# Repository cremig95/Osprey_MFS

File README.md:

# Osprey_MFS
These are the files for my Osprey MFS in the newest Versions

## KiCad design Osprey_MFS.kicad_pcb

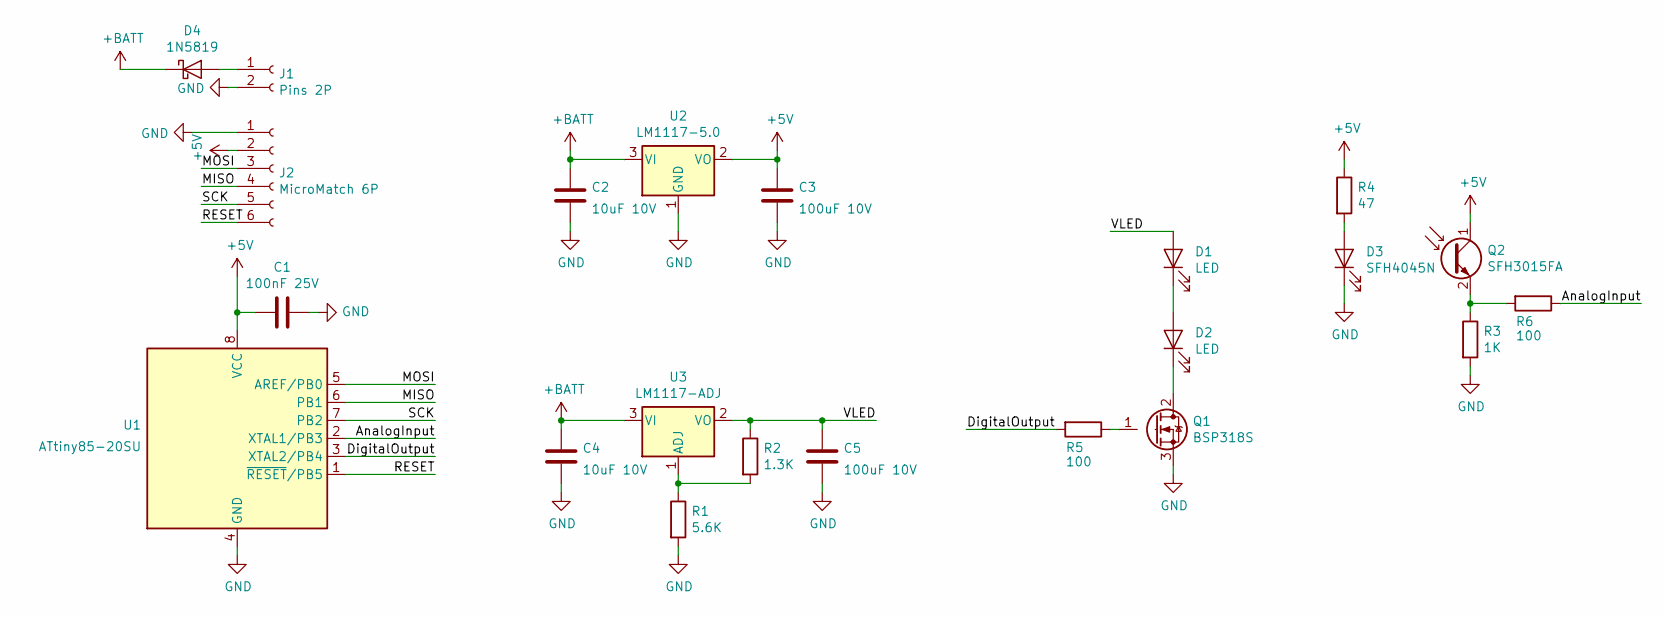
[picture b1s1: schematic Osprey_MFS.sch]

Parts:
C1: 100nF 25V; C_0603_1608Metric_Pad1.05x0.95mm_HandSolder
C2, C4: 10uF 10V; C_0603_1608Metric_Pad1.05x0.95mm_HandSolder
C3, C5: 100uF 10V; C_1210_3225Metric_Pad1.42x2.65mm_HandSolder
D1, D2: LED; LED_Cree-XQ_HandSoldering
D3: SFH4045N; LED_1210_3225Metric_Pad1.42x2.65mm_HandSolder
D4: 1N5819; D_SOD-123
J1: Pins 2P; PinHeader_1x02_P2.54mm_Vertical
J2: MicroMatch 6P; ConnectorMicromatch-6
Q1: BSP318S; SOT-223-3_TabPin2
Q2: SFH3015FA; LED_1210_3225Metric_Pad1.42x2.65mm_HandSolder
R1: 5.6K; R_0603_1608Metric_Pad1.05x0.95mm_HandSolder
R2: 1.3K; R_0603_1608Metric_Pad1.05x0.95mm_HandSolder
R3: 1K; R_0603_1608Metric_Pad1.05x0.95mm_HandSolder
R4: 47; R_0603_1608Metric_Pad1.05x0.95mm_HandSolder
R5, R6: 100; R_0603_1608Metric_Pad1.05x0.95mm_HandSolder
U1: ATtiny85-20SU; SOIJ-8_5.3x5.3mm_P1.27mm
U2: LM1117-5.0; SOT-223-3_TabPin2
U3: LM1117-ADJ; SOT-223-3_TabPin2

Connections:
+5V: C1.2, C3.1, J2.2, Q2.1 (C), R4.1, U1.8 (VCC), U2.2 (VO)
+BATT: C2.1, C4.1, D4.1 (K), U2.3 (VI), U3.3 (VI)
/AnalogInput: R6.1, U1.2 (XTAL1/PB3)
/DigitalOutput: R5.2, U1.3 (XTAL2/PB4)
/MISO: J2.4, U1.6 (PB1)
/MOSI: J2.3, U1.5 (AREF/PB0)
/RESET: J2.6, U1.1 (~RESET~/PB5)
/SCK: J2.5, U1.7 (PB2)
/VLED: C5.1, D1.2 (A), R2.1, U3.2 (VO)
GND: C1.1, C2.2, C3.2, C4.2, C5.2, D3.1 (K), J1.2, J2.1, Q1.3 (S), R1.2, R3.2, U1.4 (GND), U2.1 (GND)
unnamed: D1.1 (K), D2.2 (A)
unnamed: D2.1 (K), Q1.2 (D)
unnamed: D3.2 (A), R4.2
unnamed: D4.2 (A), J1.1
unnamed: Q1.1 (G), R5.1
unnamed: Q2.2 (E), R3.1, R6.2
unnamed: R1.1, R2.2, U3.1 (ADJ)

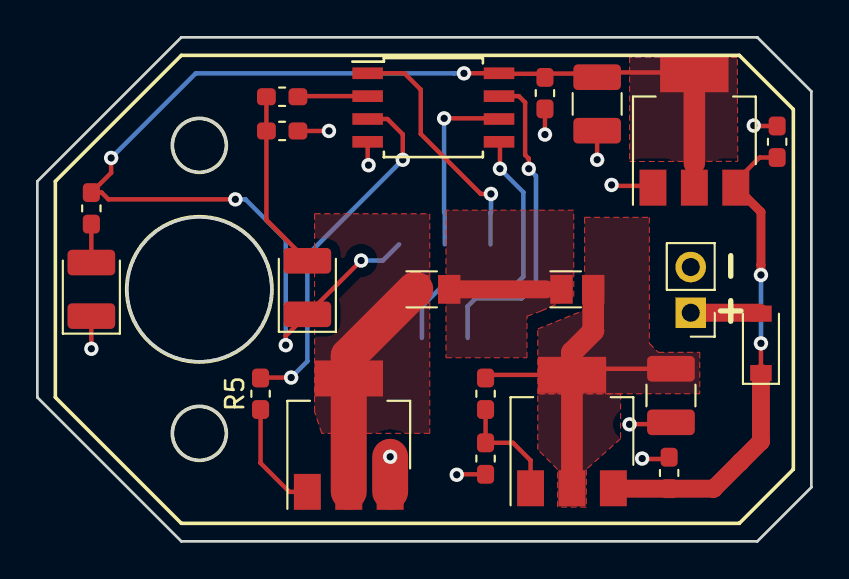
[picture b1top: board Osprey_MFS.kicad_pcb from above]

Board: 2 copper layers, 43.0 x 28.0 mm, 22 parts (1 on the bottom side), 17 nets.

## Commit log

2019-05-17 First Upload
